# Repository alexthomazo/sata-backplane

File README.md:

# SATA Backplane

This backplane is used to rotate the SATA data connector to 90°
in order to help mouting hard drive into Fractal Node 804.

The hard drives have 3.5mm between them.

The [bom](/docs/bom.csv) can be found in the docs directory.

## V1.0 Production

The V1.0 has been produced by JLCPCB, tested and working very well.

Here's some photos of the result:

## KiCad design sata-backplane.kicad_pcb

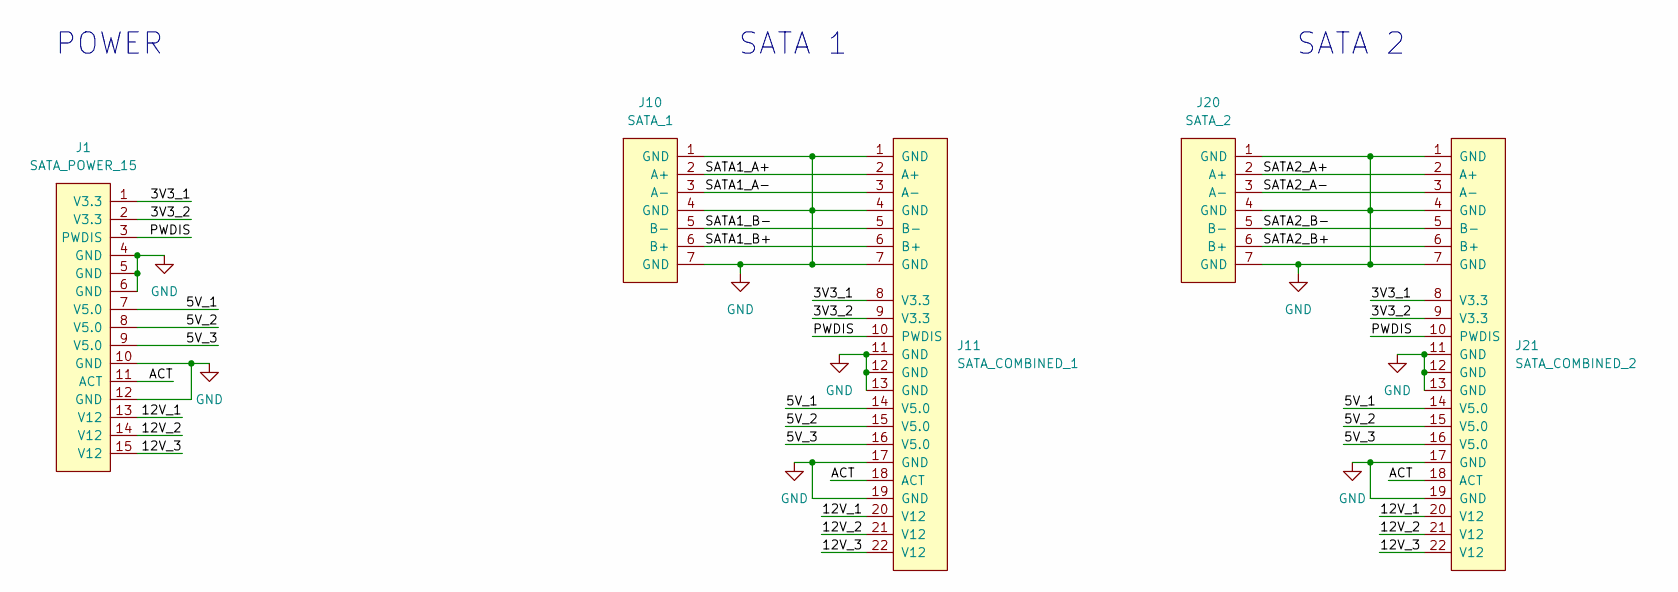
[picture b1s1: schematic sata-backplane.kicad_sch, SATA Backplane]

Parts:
J1: SATA_POWER_15; SATA_Power
J10: SATA_1; SATA_Data
J11: SATA_COMBINED_1; SATA_Combined
J20: SATA_2; SATA_Data
J21: SATA_COMBINED_2; SATA_Combined

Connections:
/3V3_1: J1.1 (V3.3), J11.8 (V3.3), J21.8 (V3.3)
/3V3_2: J1.2 (V3.3), J11.9 (V3.3), J21.9 (V3.3)
/5V_1: J1.7 (V5.0), J11.14 (V5.0), J21.14 (V5.0)
/5V_2: J1.8 (V5.0), J11.15 (V5.0), J21.15 (V5.0)
/5V_3: J1.9 (V5.0), J11.16 (V5.0), J21.16 (V5.0)
/12V_1: J1.13 (V12), J11.20 (V12), J21.20 (V12)
/12V_2: J1.14 (V12), J11.21 (V12), J21.21 (V12)
/12V_3: J1.15 (V12), J11.22 (V12), J21.22 (V12)
/ACT: J1.11 (ACT), J11.18 (ACT), J21.18 (ACT)
/PWDIS: J1.3 (PWDIS), J11.10 (PWDIS), J21.10 (PWDIS)
/SATA1_A+: J10.2 (A+), J11.2 (A+)
/SATA1_A-: J10.3 (A-), J11.3 (A-)
/SATA1_B+: J10.6 (B+), J11.6 (B+)
/SATA1_B-: J10.5 (B-), J11.5 (B-)
/SATA2_A+: J20.2 (A+), J21.2 (A+)
/SATA2_A-: J20.3 (A-), J21.3 (A-)
/SATA2_B+: J20.6 (B+), J21.6 (B+)
/SATA2_B-: J20.5 (B-), J21.5 (B-)
GND: J1.4 (GND), J1.5 (GND), J1.6 (GND), J1.10 (GND), J1.12 (GND), J10.1 (GND), J10.4 (GND), J10.7 (GND), J11.1 (GND), J11.4 (GND), J11.7 (GND), J11.11 (GND), J11.12 (GND), J11.13 (GND), J11.17 (GND), J11.19 (GND), J20.1 (GND), J20.4 (GND), J20.7 (GND), J21.1 (GND), J21.4 (GND), J21.7 (GND), J21.11 (GND), J21.12 (GND), J21.13 (GND), J21.17 (GND), J21.19 (GND)

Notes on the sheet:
SATA 1
SATA 2
POWER

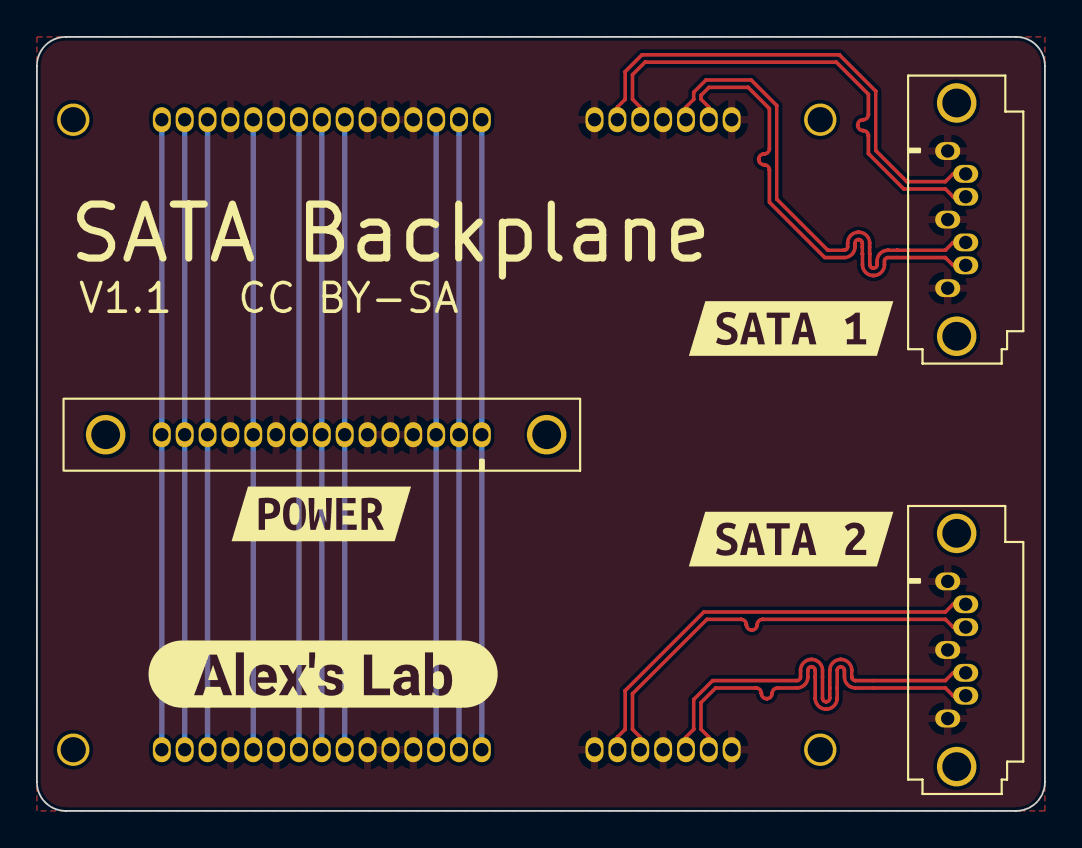
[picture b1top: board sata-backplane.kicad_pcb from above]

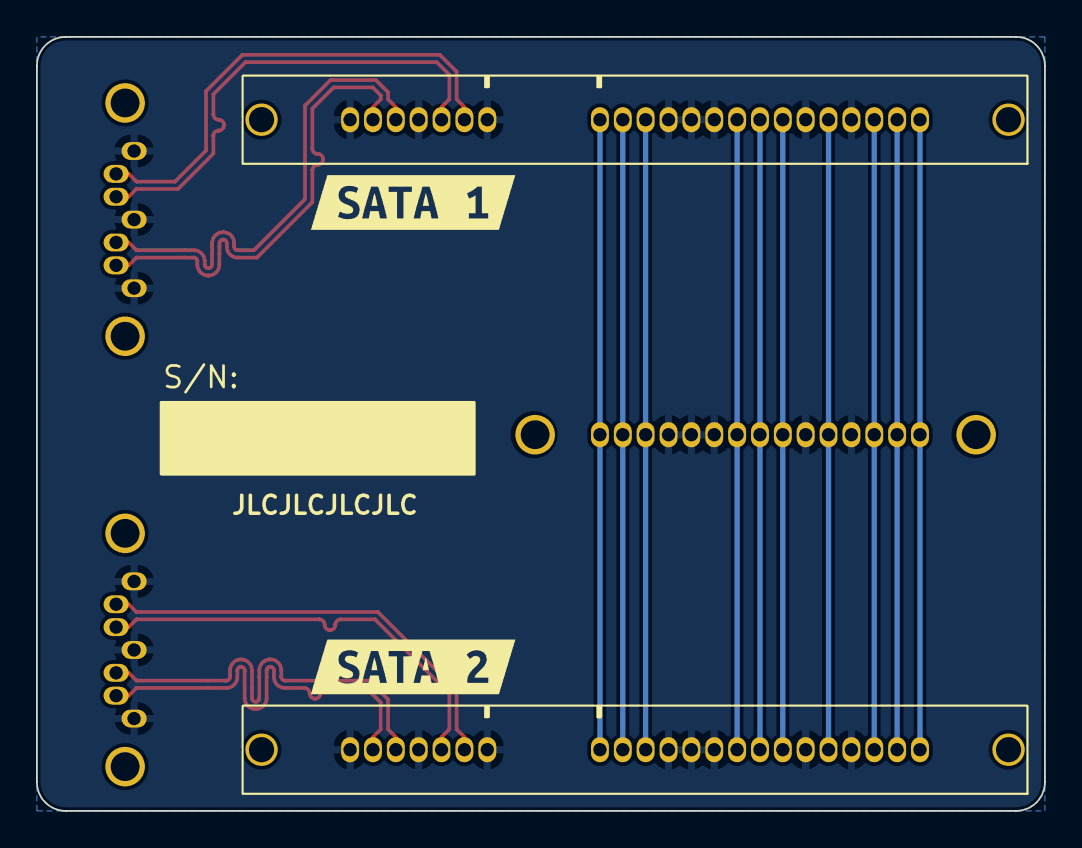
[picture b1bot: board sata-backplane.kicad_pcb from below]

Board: 4 copper layers, 56.0 x 43.0 mm, 11 parts (4 on the bottom side), 19 nets.

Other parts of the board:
kibuzzard-63B1B17B, kibuzzard-63B1B17B#2: G***; kibuzzard-63B1B17B
kibuzzard-63B1B127: G***; kibuzzard-63B1B127
kibuzzard-63B1B175, kibuzzard-63B1B175#2: G***; kibuzzard-63B1B175
kibuzzard-63B1B180: G***; kibuzzard-63B1B180

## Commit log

2023-01-01 Initial commit with first revision
2023-01-06 Update PCB with final touch
2023-01-06 Add tmp in .gitignore
2023-01-06 [docs] Add Readme and PCB 3D view
2023-04-26 Update connectors with V1.0 experience
2023-04-26 Update docs with V1.0 production

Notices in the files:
sata-backplane.kicad_pcb:
V1.1 CC BY-SA
sata-backplane.kicad_sch:
GPL v3
